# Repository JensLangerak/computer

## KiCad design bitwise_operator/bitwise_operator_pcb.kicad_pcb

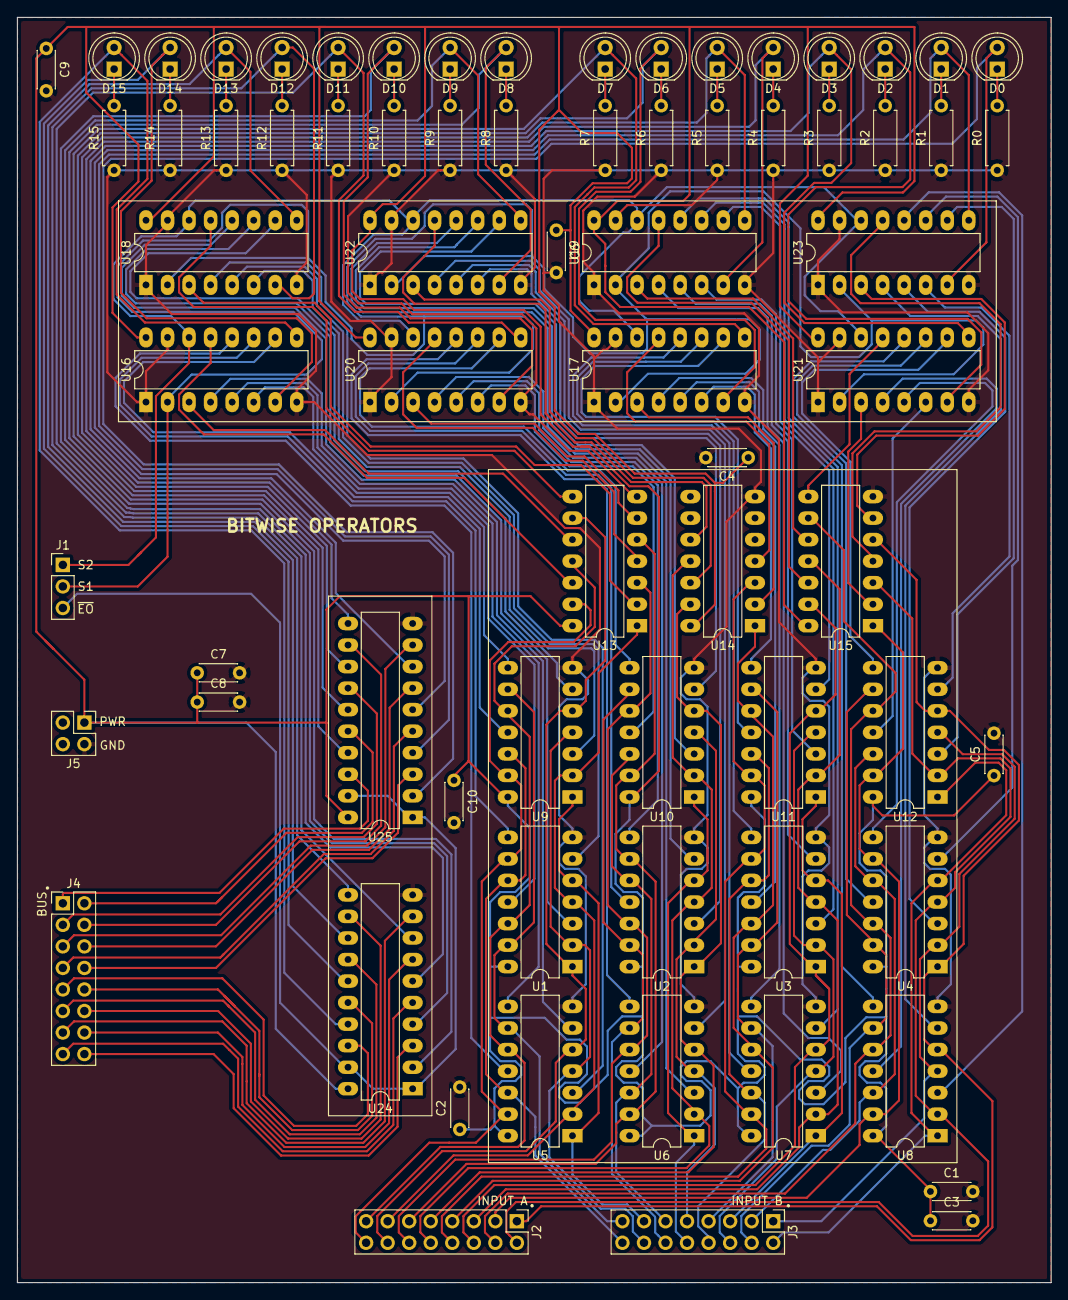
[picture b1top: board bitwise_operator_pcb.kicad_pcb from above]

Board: 2 copper layers, 121.9 x 149.2 mm, 72 parts (0 on the bottom side), 149 nets.

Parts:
C1, C2, C3, C4, C5, C6, C7, C8, C9, C10: 0.1µF; C_Disc_D4.3mm_W1.9mm_P5.00mm
D0, D1, D2, D3, D4, D5, D6, D7, D8, D9, D10, D11, D12, D13, D14, D15: LED_ALT; LED_D5.0mm
J1: Conn_01x03; PinHeader_1x03_P2.54mm_Vertical
J2, J3, J4: Conn_02x08_Odd_Even; PinHeader_2x08_P2.54mm_Vertical
J5: Conn_02x02_Odd_Even; PinHeader_2x02_P2.54mm_Vertical
R0, R1, R2, R3, R4, R5, R6, R7, R8, R9, R10, R11, R12, R13, R14, R15: 5k; R_Axial_DIN0207_L6.3mm_D2.5mm_P7.62mm_Horizontal
U1, U2, U3, U4: 74LS08; DIP-14_W7.62mm_LongPads
U5, U6, U7, U8: 74LS32; DIP-14_W7.62mm_LongPads
U9, U10, U11, U12: 74LS86; DIP-14_W7.62mm_LongPads
U13, U14, U15: 74LS04; DIP-14_W7.62mm_LongPads
U16, U17, U18, U19, U20, U21, U22, U23: 74LS153; DIP-16_W7.62mm_LongPads
U24, U25: 74LS244; DIP-20_W7.62mm_LongPads

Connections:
/CONN BUS A/D0: J2.1, U4.1, U8.5, U12.5, U15.5
/CONN BUS A/D1: J2.2, U4.4, U8.2, U12.2, U15.3
/CONN BUS A/D2: J2.3, U4.9, U8.13, U12.13, U15.1
/CONN BUS A/D3: J2.4, U4.12, U8.10, U12.10, U15.9
/CONN BUS A/D4: J2.5, U3.4, U7.2, U11.2, U15.11
/CONN BUS A/D5: J2.6, U3.1, U7.5, U11.5, U15.13
/CONN BUS A/D6: J2.7, U3.12, U7.10, U11.10, U14.1
/CONN BUS A/D7: J2.8, U3.9, U7.13, U11.13, U14.3
/CONN BUS A/D8: J2.9, U2.1, U6.5, U10.5, U14.13
/CONN BUS A/D9: J2.10, U2.4, U6.2, U10.2, U14.11
/CONN BUS A/D10: J2.11, U2.9, U6.13, U10.13, U13.5
/CONN BUS A/D11: J2.12, U2.12, U6.10, U10.10, U13.3
/CONN BUS A/D12: J2.13, U1.4, U5.2, U9.2, U13.1
/CONN BUS A/D13: J2.14, U1.1, U5.5, U9.5, U13.9
/CONN BUS A/D14: J2.15, U1.12, U5.10, U9.10, U13.11
/CONN BUS A/D15: J2.16, U1.9, U5.13, U9.13, U13.13
/CONN BUS B/D0: J3.1, U4.2, U8.4, U12.4
/CONN BUS B/D1: J3.2, U4.5, U8.1, U12.1
/CONN BUS B/D2: J3.3, U4.10, U8.12, U12.12
/CONN BUS B/D3: J3.4, U4.13, U8.9, U12.9
/CONN BUS B/D4: J3.5, U3.5, U7.1, U11.1
/CONN BUS B/D5: J3.6, U3.2, U7.4, U11.4
/CONN BUS B/D6: J3.7, U3.13, U7.9, U11.9
/CONN BUS B/D7: J3.8, U3.10, U7.12, U11.12
/CONN BUS B/D8: J3.9, U2.2, U6.4, U10.4
/CONN BUS B/D9: J3.10, U2.5, U6.1, U10.1
/CONN BUS B/D10: J3.11, U2.10, U6.12, U10.12
/CONN BUS B/D11: J3.12, U2.13, U6.9, U10.9
/CONN BUS B/D12: J3.13, U1.5, U5.1, U9.1
/CONN BUS B/D13: J3.14, U1.2, U5.4, U9.4
/CONN BUS B/D14: J3.15, U1.13, U5.9, U9.9
/CONN BUS B/D15: J3.16, U1.10, U5.12, U9.12
/CONN BUS DATA/D0: J4.1, U25.18
/CONN BUS DATA/D1: J4.2, U25.16
/CONN BUS DATA/D2: J4.3, U25.14
/CONN BUS DATA/D3: J4.4, U25.12
/CONN BUS DATA/D4: J4.5, U25.9
/CONN BUS DATA/D5: J4.6, U25.7
/CONN BUS DATA/D6: J4.7, U25.5
/CONN BUS DATA/D7: J4.8, U25.3
/CONN BUS DATA/D8: J4.9, U24.18
/CONN BUS DATA/D9: J4.10, U24.16
/CONN BUS DATA/D10: J4.11, U24.14
/CONN BUS DATA/D11: J4.12, U24.12
/CONN BUS DATA/D12: J4.13, U24.9
/CONN BUS DATA/D13: J4.14, U24.7
/CONN BUS DATA/D14: J4.15, U24.5
/CONN BUS DATA/D15: J4.16, U24.3
/LOGIC UNIT/BUS MULTIPLEXER/D_A0: U12.6, U23.6
/LOGIC UNIT/BUS MULTIPLEXER/D_A1: U12.3, U23.10
/LOGIC UNIT/BUS MULTIPLEXER/D_A2: U12.11, U21.6
/LOGIC UNIT/BUS MULTIPLEXER/D_A3: U12.8, U21.10
/LOGIC UNIT/BUS MULTIPLEXER/D_A4: U11.3, U19.6
/LOGIC UNIT/BUS MULTIPLEXER/D_A5: U11.6, U19.10
/LOGIC UNIT/BUS MULTIPLEXER/D_A6: U11.8, U17.6
/LOGIC UNIT/BUS MULTIPLEXER/D_A7: U11.11, U17.10
/LOGIC UNIT/BUS MULTIPLEXER/D_A8: U10.6, U22.6
/LOGIC UNIT/BUS MULTIPLEXER/D_A9: U10.3, U22.10
/LOGIC UNIT/BUS MULTIPLEXER/D_A10: U10.11, U20.6
/LOGIC UNIT/BUS MULTIPLEXER/D_A11: U10.8, U20.10
/LOGIC UNIT/BUS MULTIPLEXER/D_A12: U9.3, U18.6
/LOGIC UNIT/BUS MULTIPLEXER/D_A13: U9.6, U18.10
/LOGIC UNIT/BUS MULTIPLEXER/D_A14: U9.8, U16.6
/LOGIC UNIT/BUS MULTIPLEXER/D_A15: U9.11, U16.10
/LOGIC UNIT/BUS MULTIPLEXER/D_B0: U4.3, U23.5
/LOGIC UNIT/BUS MULTIPLEXER/D_B1: U4.6, U23.11
/LOGIC UNIT/BUS MULTIPLEXER/D_B2: U4.8, U21.5
/LOGIC UNIT/BUS MULTIPLEXER/D_B3: U4.11, U21.11
/LOGIC UNIT/BUS MULTIPLEXER/D_B4: U3.6, U19.5
/LOGIC UNIT/BUS MULTIPLEXER/D_B5: U3.3, U19.11
/LOGIC UNIT/BUS MULTIPLEXER/D_B6: U3.11, U17.5
/LOGIC UNIT/BUS MULTIPLEXER/D_B7: U3.8, U17.11
/LOGIC UNIT/BUS MULTIPLEXER/D_B8: U2.3, U22.5
/LOGIC UNIT/BUS MULTIPLEXER/D_B9: U2.6, U22.11
/LOGIC UNIT/BUS MULTIPLEXER/D_B10: U2.8, U20.5
/LOGIC UNIT/BUS MULTIPLEXER/D_B11: U2.11, U20.11
/LOGIC UNIT/BUS MULTIPLEXER/D_B12: U1.6, U18.5
/LOGIC UNIT/BUS MULTIPLEXER/D_B13: U1.3, U18.11
/LOGIC UNIT/BUS MULTIPLEXER/D_B14: U1.11, U16.5
/LOGIC UNIT/BUS MULTIPLEXER/D_B15: U1.8, U16.11
/LOGIC UNIT/BUS MULTIPLEXER/D_C0: U8.6, U23.4
/LOGIC UNIT/BUS MULTIPLEXER/D_C1: U8.3, U23.12
/LOGIC UNIT/BUS MULTIPLEXER/D_C2: U8.11, U21.4
/LOGIC UNIT/BUS MULTIPLEXER/D_C3: U8.8, U21.12
/LOGIC UNIT/BUS MULTIPLEXER/D_C4: U7.3, U19.4
/LOGIC UNIT/BUS MULTIPLEXER/D_C5: U7.6, U19.12
/LOGIC UNIT/BUS MULTIPLEXER/D_C6: U7.8, U17.4
/LOGIC UNIT/BUS MULTIPLEXER/D_C7: U7.11, U17.12
/LOGIC UNIT/BUS MULTIPLEXER/D_C8: U6.6, U22.4
/LOGIC UNIT/BUS MULTIPLEXER/D_C9: U6.3, U22.12
/LOGIC UNIT/BUS MULTIPLEXER/D_C10: U6.11, U20.4
/LOGIC UNIT/BUS MULTIPLEXER/D_C11: U6.8, U20.12
/LOGIC UNIT/BUS MULTIPLEXER/D_C12: U5.3, U18.4
/LOGIC UNIT/BUS MULTIPLEXER/D_C13: U5.6, U18.12
/LOGIC UNIT/BUS MULTIPLEXER/D_C14: U5.8, U16.4
/LOGIC UNIT/BUS MULTIPLEXER/D_C15: U5.11, U16.12
/LOGIC UNIT/BUS MULTIPLEXER/D_D0: U15.6, U23.3
/LOGIC UNIT/BUS MULTIPLEXER/D_D1: U15.4, U23.13
/LOGIC UNIT/BUS MULTIPLEXER/D_D2: U15.2, U21.3
/LOGIC UNIT/BUS MULTIPLEXER/D_D3: U15.8, U21.13
/LOGIC UNIT/BUS MULTIPLEXER/D_D4: U15.10, U19.3
/LOGIC UNIT/BUS MULTIPLEXER/D_D5: U15.12, U19.13
/LOGIC UNIT/BUS MULTIPLEXER/D_D6: U14.2, U17.3
/LOGIC UNIT/BUS MULTIPLEXER/D_D7: U14.4, U17.13
/LOGIC UNIT/BUS MULTIPLEXER/D_D8: U14.12, U22.3
/LOGIC UNIT/BUS MULTIPLEXER/D_D9: U14.10, U22.13
/LOGIC UNIT/BUS MULTIPLEXER/D_D10: U13.6, U20.3
/LOGIC UNIT/BUS MULTIPLEXER/D_D11: U13.4, U20.13
/LOGIC UNIT/BUS MULTIPLEXER/D_D12: U13.2, U18.3
/LOGIC UNIT/BUS MULTIPLEXER/D_D13: U13.8, U18.13
/LOGIC UNIT/BUS MULTIPLEXER/D_D14: U13.10, U16.3
/LOGIC UNIT/BUS MULTIPLEXER/D_D15: U13.12, U16.13
/LOGIC UNIT/LEDS/D0: D0.2, U23.7, U25.2
/LOGIC UNIT/LEDS/D1: D1.2, U23.9, U25.4
/LOGIC UNIT/LEDS/D2: D2.2, U21.7, U25.6
/LOGIC UNIT/LEDS/D3: D3.2, U21.9, U25.8
/LOGIC UNIT/LEDS/D4: D4.2, U19.7, U25.11
/LOGIC UNIT/LEDS/D5: D5.2, U19.9, U25.13
/LOGIC UNIT/LEDS/D6: D6.2, U17.7, U25.15
/LOGIC UNIT/LEDS/D7: D7.2, U17.9, U25.17
/LOGIC UNIT/LEDS/D8: D8.2, U22.7, U24.2
/LOGIC UNIT/LEDS/D9: D9.2, U22.9, U24.4
/LOGIC UNIT/LEDS/D10: D10.2, U20.7, U24.6
/LOGIC UNIT/LEDS/D11: D11.2, U20.9, U24.8
/LOGIC UNIT/LEDS/D12: D12.2, U18.7, U24.11
/LOGIC UNIT/LEDS/D13: D13.2, U18.9, U24.13
/LOGIC UNIT/LEDS/D14: D14.2, U16.7, U24.15
/LOGIC UNIT/LEDS/D15: D15.2, U16.9, U24.17
/LOGIC UNIT/S0: J1.1, U16.14, U17.14, U18.14, U19.14, U20.14, U21.14, U22.14, U23.14
/LOGIC UNIT/S1: J1.2, U16.2, U17.2, U18.2, U19.2, U20.2, U21.2, U22.2, U23.2
/LOGIC UNIT/~EO~: J1.3, U24.1, U24.19, U25.1, U25.19
GND: C1.2, C2.2, C3.2, C4.2, C5.2, C6.2, C7.2, C8.2, C9.2, C10.2, J5.2, R0.1, R1.1, R2.1, R3.1, R4.1, R5.1, R6.1, R7.1, R8.1, R9.1, R10.1, R11.1, R12.1, R13.1, R14.1, R15.1, U1.7, U2.7, U3.7, U4.7, U5.7, U6.7, U7.7, U8.7, U9.7, U10.7, U11.7, U12.7, U13.7, U14.7, U15.7, U16.1, U16.8, U16.15, U17.1, U17.8, U17.15, U18.1, U18.8, U18.15, U19.1, U19.8, U19.15, U20.1, U20.8, U20.15, U21.1, U21.8, U21.15, U22.1, U22.8, U22.15, U23.1, U23.8, U23.15, U24.10, U25.10
unnamed: D0.1, R0.2
unnamed: D1.1, R1.2
unnamed: D2.1, R2.2
unnamed: D3.1, R3.2
unnamed: D4.1, R4.2
unnamed: D5.1, R5.2
unnamed: D6.1, R6.2
unnamed: D7.1, R7.2
unnamed: D8.1, R8.2
unnamed: D9.1, R9.2
unnamed: D10.1, R10.2
unnamed: D11.1, R11.2
unnamed: D12.1, R12.2
unnamed: D13.1, R13.2
unnamed: D14.1, R14.2
unnamed: D15.1, R15.2
VCC: C1.1, C2.1, C3.1, C4.1, C5.1, C6.1, C7.1, C8.1, C9.1, C10.1, J5.1, U1.14, U2.14, U3.14, U4.14, U5.14, U6.14, U7.14, U8.14, U9.14, U10.14, U11.14, U12.14, U13.14, U14.14, U15.14, U16.16, U17.16, U18.16, U19.16, U20.16, U21.16, U22.16, U23.16, U24.20, U25.20

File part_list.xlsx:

| 4x | register | dus voor 2 onderdelen
 |  |  |  |  |  |  |  |  |  | Reg extra: | 1 |  |  |  |  |  |  | LS |  |  |  |  |  | HCT
 | ALU | Bit shifter | Bitwise Operator | Buttons | CU | Display | Memory | Mem programmer | Program counter | Register | Register Extra |  |  |  |  | TOT= | Shop unit cost | reichelt | mouser | conrad | kiwi |  |  | reichelt | mouser | conrad
Capacitor 0.1uF | 4 | 3 | 10 | 2 | 5 | 2 | 2 | 4 | 3 | 2 | 2 |  |  |  |  | 39
RED LED | 16 | 16 | 16 | 5 | 60 |  | 16 | 2 | 16 | 16 | 16 |  |  |  |  | 179 |  | 9.0999999999999998E-2
PIN HEADER | 42 | 24 | 23 | 22 | 107 | 26 | 38 |  | 24 | 22 | 22 |  |  |  |  | 350 |  | 0,03 (per 8)
Resitor 5K | 16 | 16 | 16 | 10 | 83 |  | 16 |  | 16 | 16 | 16 |  |  |  |  | 205
SW_PUSH |  |  |  | 5 | 1 |  |  |  |  |  | 0 |  |  |  |  | 6
Capacitor 1uF MKP4-250 ? of mks probeer allebij |  |  |  |  |  | 9 |  |  |  |  | 0 |  |  |  |  | 9
Resitor 220 |  |  |  |  |  |  |  | 2 |  |  | 0 |  |  |  |  | 2
Long pinheader arduino Stapel Header, normale pin headers |  |  |  |  |  |  |  | 34 |  |  | 0 |  |  |  |  | 34 |  |  |  |  | 2.5
Resistor 50K |  |  |  |  |  |  |  |  | 1 |  | 0 |  |  |  |  | 1
 |  |  |  |  |  |  |  |  |  |  | 0 |  |  |  |  | 0
74LS00 | 1 |  |  |  |  |  |  |  |  |  | 0 |  |  |  |  | 1 |  | 1.01 | 0.54 |  |  |  |  | 0.34 | 0.40699999999999997
74LS02 | 2 |  |  |  |  |  |  |  |  |  | 0 |  |  |  |  | 2 |  | 0.62 | 0.55100000000000005 |  |  |  |  | 0.3 | 0.40699999999999997
74LS04 |  |  | 3 | 1 | 1 |  | 1 |  |  |  | 0 |  |  |  |  | 6 |  | 0.68 | 0.61799999999999999 |  |  |  |  | 0.24 | 0.40699999999999997
74LS08 | 2 |  | 4 |  | 1 |  |  |  |  |  | 0 |  |  |  |  | 7 |  | 0.7 | 0.55900000000000005 |  |  |  |  | 0.22 | 0.40699999999999997
74LS139 |  |  |  |  |  |  |  | 1 |  |  | 0 |  |  |  |  | 1 |  | 0.82 | 0.71099999999999997 |  |  |  |  | 0.53 | 0.38100000000000001
74LS153 |  |  | 8 |  |  |  |  |  |  |  | 0 |  |  |  |  | 8 |  | 0.26 | 0.76200000000000001 |  |  |  |  | 0.23 | 0.55900000000000005
74LS163 |  |  |  |  | 1 |  |  |  | 4 |  | 0 |  |  |  |  | 5 |  | 0.44 | 0.66900000000000004 |  |  |  |  | 0.28000000000000003 | 0.5
74LS194 |  | 4 |  |  |  |  |  |  |  |  | 0 |  |  |  |  | 4 |  | 0.8 | 1.32 |  |  |  |  |  | 0.70299999999999996
74LS244 | 2 | 2 | 2 | 2 | 2 | 2 |  |  | 2 | 2 | 2 |  |  |  |  | 18 |  | 0.79 | 0.76200000000000001 |  |  |  |  | 0.37 | 0.49099999999999999
74LS245 |  |  |  |  |  |  | 2 | 1 |  |  | 0 |  |  |  |  | 3 |  | 0.82 |  |  |  |  |  | 0.45
74LS283 | 4 |  |  |  |  |  |  |  |  |  | 0 |  |  |  |  | 4 |  |  |  |  |  |  |  |  |  | 0.76
74LS32 |  |  | 4 |  |  |  |  |  |  |  | 0 |  |  |  |  | 4 |  | 0.57999999999999996 | 0.51700000000000002 |  |  |  |  | 0.55000000000000004 | 0.40699999999999997
74LS375 |  |  |  | 2 |  |  |  |  |  |  | 0 |  |  |  |  | 2 |  | 0.32 | 0.97399999999999998
74LS377 |  |  |  |  |  |  |  | 3 |  | 2 | 2 |  |  |  |  | 7 |  |  | 0.76200000000000001 |  |  |  |  | 0.39 | 0.55900000000000005
74LS386 MOET waarschijnlijk 136 zijn, prijzen daarvoor, denk eigenlijk 86, dus 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 | 4 |  |  |  |  |  |  |  |  |  | 0 |  |  |  |  | 4 |  |  | 0.72799999999999998 |  |  |  |  |  | 0.65200000000000002
74LS86 |  |  | 4 |  |  |  |  |  |  |  | 0 |  |  |  |  | 4 |  | 0.7 | 0.51700000000000002 |  |  |  |  |  | 0.58399999999999996
 |  |  |  |  |  |  |  |  |  |  | 0 |  |  |  |  | 0
 |  |  |  |  |  |  |  |  |  |  | 0 |  |  |  |  | 0
 |  |  |  |  |  |  |  |  |  |  | 0 |  |  |  |  | 0
Header jumpers |  |  |  |  | 8 |  |  |  |  |  | 0 |  |  |  |  | 8 |  | 0.02
SST39SF010A-70-4C-PHE |  |  |  |  | 6 |  |  |  |  |  | 0 |  |  |  |  | 6 |  | 1.68 | 1.05 | 1.94
SOCKET SST39SF010A-70-4C-PHE pin 32: w: 15:24 |  |  |  |  | 6 |  |  | 1 |  |  | 0 |  |  |  |  | 7 |  | 0.54 | 1.3 |  |  |  |  | https://www.reichelt.nl/ic-socket-32-polig-super-plat-gedraa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
NHD-C12864LZ-FSW-FBW-3V3 |  |  |  |  |  | 1 |  |  |  |  | 0 |  |  |  |  | 1 |  |  | 13.91
CD40109BE |  |  |  |  |  | 4 |  |  |  |  | 0 |  |  |  |  | 4 |  |  | 0.747
LP2950-3.0_TO92 of MCP1702-3002E/TO TODO nog beslitssen |  |  |  |  |  | 1 |  |  |  |  | 0 |  |  |  |  | 1
AT28C256-15PU |  |  |  |  |  |  | 2 |  |  |  | 0 |  |  |  |  | 2 |  | 10.69 | 7.52
SOCKETS AT28C256-15PU |  |  |  |  |  |  | 2 | 1 |  |  | 0 |  |  |  |  | 3 |  | 0.47 | 0.39
Control LEDS (BLUE) |  |  |  |  | 48 |  |  |  |  |  |  |  |  |  |  | 48 |  | 0.28000000000000003
CLK LED (GREEN) |  |  |  |  | 1 |  |  |  |  |  |  |  |  |  |  | 1 |  | 0.17299999999999999
COUNTER LED (BLUE) |  |  |  |  | 4 |  |  |  |  |  |  |  |  |  |  | 4 |  | 0.28000000000000003
FLAG LEDS (ORANGE) |  |  |  |  | 4 |  |  |  |  |  |  |  |  |  |  | 4
YELLOW LED |  |  |  |  |  |  |  |  |  |  |  |  |  |  |  |  |  | 0.14199999999999999
white |  |  |  |  |  |  |  |  |  |  |  |  |  |  |  |  |  | 0.24

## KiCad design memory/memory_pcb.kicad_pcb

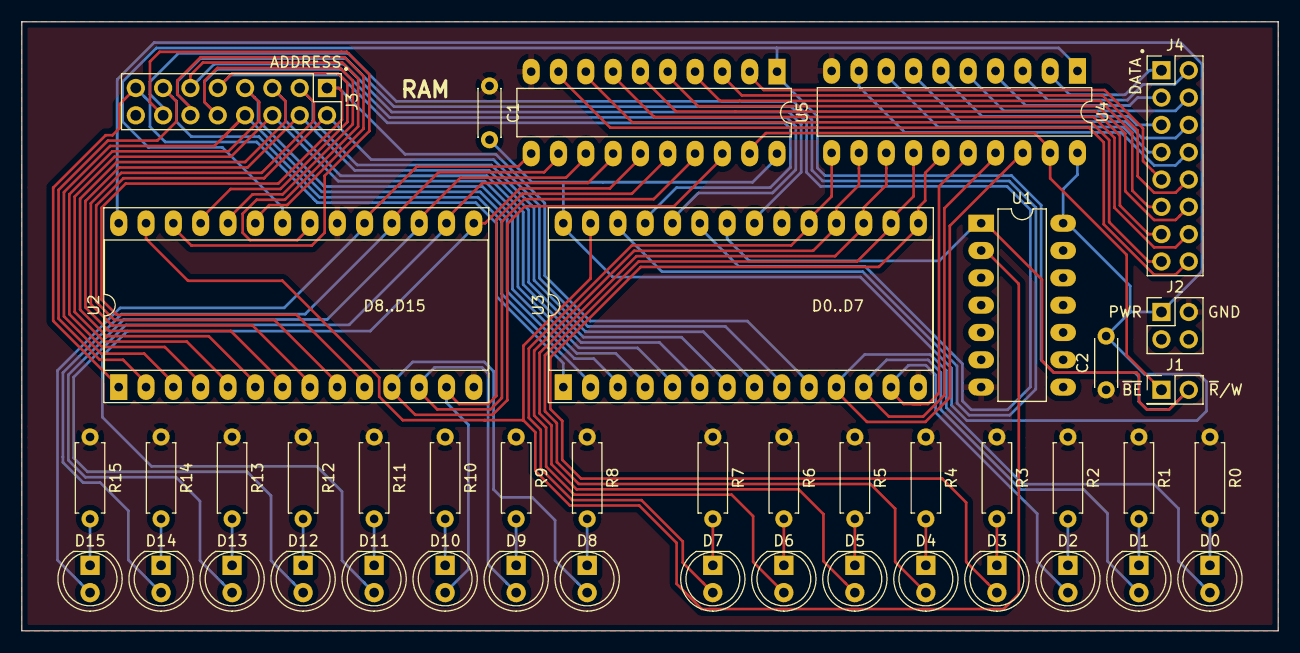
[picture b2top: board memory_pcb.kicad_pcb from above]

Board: 2 copper layers, 116.8 x 56.6 mm, 43 parts (0 on the bottom side), 68 nets.

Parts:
C1, C2: 0.1µF; C_Disc_D4.3mm_W1.9mm_P5.00mm
D0, D1, D2, D3, D4, D5, D6, D7, D8, D9, D10, D11, D12, D13, D14, D15: LED_ALT; LED_D5.0mm
J1: Conn_02x01; PinHeader_2x01_P2.54mm_Vertical
J2: Conn_02x02_Odd_Even; PinHeader_2x02_P2.54mm_Vertical
J3, J4: Conn_02x08_Odd_Even; PinHeader_2x08_P2.54mm_Vertical
R0, R1, R2, R3, R4, R5, R6, R7, R8, R9, R10, R11, R12, R13, R14, R15: 5k; R_Axial_DIN0207_L6.3mm_D2.5mm_P7.62mm_Horizontal
U1: 74LS04; DIP-14_W7.62mm_LongPads
U2, U3: AT28C256-15PU; DIP-28_W15.24mm_Socket_LongPads
U4, U5: 74LS245; DIP-20_W7.62mm_LongPads

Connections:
/CON BUS DATA/D0: J4.1, U4.2
/CON BUS DATA/D1: J4.2, U4.3
/CON BUS DATA/D2: J4.3, U4.4
/CON BUS DATA/D3: J4.4, U4.5
/CON BUS DATA/D4: J4.5, U4.6
/CON BUS DATA/D5: J4.6, U4.7
/CON BUS DATA/D6: J4.7, U4.8
/CON BUS DATA/D7: J4.8, U4.9
/CON BUS DATA/D8: J4.9, U5.2
/CON BUS DATA/D9: J4.10, U5.3
/CON BUS DATA/D10: J4.11, U5.4
/CON BUS DATA/D11: J4.12, U5.5
/CON BUS DATA/D12: J4.13, U5.6
/CON BUS DATA/D13: J4.14, U5.7
/CON BUS DATA/D14: J4.15, U5.8
/CON BUS DATA/D15: J4.16, U5.9
/memory/A0: J3.1, U2.10, U3.10
/memory/A1: J3.2, U2.9, U3.9
/memory/A2: J3.3, U2.8, U3.8
/memory/A3: J3.4, U2.7, U3.7
/memory/A4: J3.5, U2.6, U3.6
/memory/A5: J3.6, U2.5, U3.5
/memory/A6: J3.7, U2.4, U3.4
/memory/A7: J3.8, U2.3, U3.3
/memory/A8: J3.9, U2.25, U3.25
/memory/A9: J3.10, U2.24, U3.24
/memory/A10: J3.11, U2.21, U3.21
/memory/A11: J3.12, U2.23, U3.23
/memory/A12: J3.13, U2.2, U3.2
/memory/A13: J3.14, U2.26, U3.26
/memory/A14: J3.15, U2.1, U3.1
/memory/D0: D0.2, U3.11, U4.18
/memory/D1: D1.2, U3.12, U4.17
/memory/D2: D2.2, U3.13, U4.16
/memory/D3: D3.2, U3.15, U4.15
/memory/D4: D4.2, U3.16, U4.14
/memory/D5: D5.2, U3.17, U4.13
/memory/D6: D6.2, U3.18, U4.12
/memory/D7: D7.2, U3.19, U4.11
/memory/D8: D8.2, U2.11, U5.18
/memory/D9: D9.2, U2.12, U5.17
/memory/D10: D10.2, U2.13, U5.16
/memory/D11: D11.2, U2.15, U5.15
/memory/D12: D12.2, U2.16, U5.14
/memory/D13: D13.2, U2.17, U5.13
/memory/D14: D14.2, U2.18, U5.12
/memory/D15: D15.2, U2.19, U5.11
/memory/~WE~: U1.2, U2.27, U3.27
/~BE~: J1.1, U4.19, U5.19
/~R~-W: J1.2, U1.1, U2.22, U3.22, U4.1, U5.1
GND: C1.1, C2.1, J2.2, R0.1, R1.1, R2.1, R3.1, R4.1, R5.1, R6.1, R7.1, R8.1, R9.1, R10.1, R11.1, R12.1, R13.1, R14.1, R15.1, U1.7, U2.14, U2.20, U3.14, U3.20, U4.10, U5.10
unnamed: D0.1, R0.2
unnamed: D1.1, R1.2
unnamed: D2.1, R2.2
unnamed: D3.1, R3.2
unnamed: D4.1, R4.2
unnamed: D5.1, R5.2
unnamed: D6.1, R6.2
unnamed: D7.1, R7.2
unnamed: D8.1, R8.2
unnamed: D9.1, R9.2
unnamed: D10.1, R10.2
unnamed: D11.1, R11.2
unnamed: D12.1, R12.2
unnamed: D13.1, R13.2
unnamed: D14.1, R14.2
unnamed: D15.1, R15.2
VCC: C1.2, C2.2, J2.1, U1.14, U2.28, U3.28, U4.20, U5.20

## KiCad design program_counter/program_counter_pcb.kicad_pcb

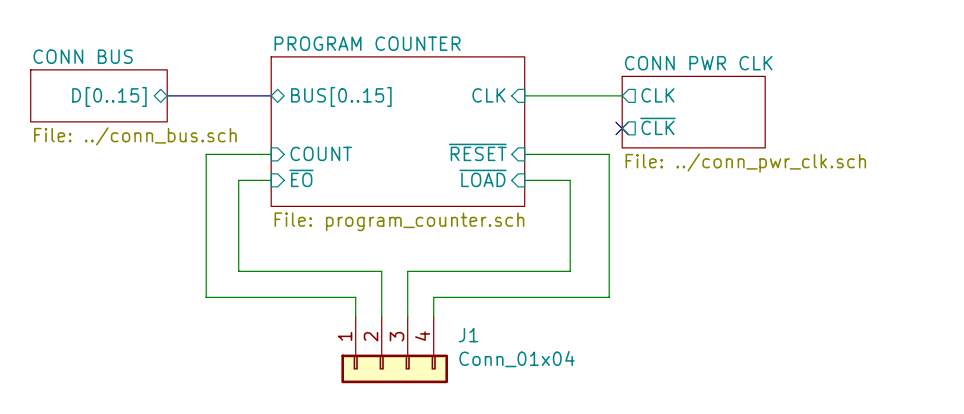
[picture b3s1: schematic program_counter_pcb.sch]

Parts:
J1: Conn_01x04; PinHeader_1x04_P2.54mm_Vertical

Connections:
/PROGRAM COUNTER/COUNT: J1.1; also elsewhere on the board
/PROGRAM COUNTER/~EO~: J1.2; also elsewhere on the board
/PROGRAM COUNTER/~LOAD~: J1.3; also elsewhere on the board
/PROGRAM COUNTER/~RESET~: J1.4; also elsewhere on the board

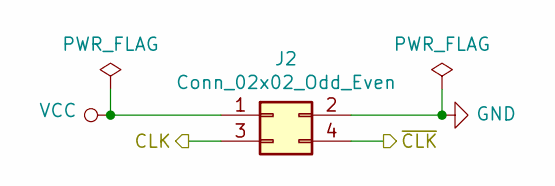
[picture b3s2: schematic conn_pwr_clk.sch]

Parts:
J2: Conn_02x02_Odd_Even; PinHeader_2x02_P2.54mm_Vertical

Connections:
/CONN PWR CLK/CLK: J2.3; also elsewhere on the board
/CONN PWR CLK/~CLK~: J2.4
GND: J2.2; also elsewhere on the board
VCC: J2.1; also elsewhere on the board

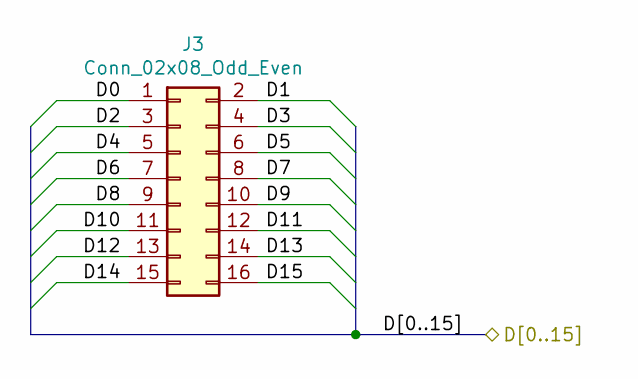
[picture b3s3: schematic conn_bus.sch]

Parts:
J3: Conn_02x08_Odd_Even; PinHeader_2x08_P2.54mm_Vertical

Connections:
/PROGRAM COUNTER/B0: J3.1; also elsewhere on the board
/PROGRAM COUNTER/B1: J3.2; also elsewhere on the board
/PROGRAM COUNTER/B2: J3.3; also elsewhere on the board
/PROGRAM COUNTER/B3: J3.4; also elsewhere on the board
/PROGRAM COUNTER/B4: J3.5; also elsewhere on the board
/PROGRAM COUNTER/B5: J3.6; also elsewhere on the board
/PROGRAM COUNTER/B6: J3.7; also elsewhere on the board
/PROGRAM COUNTER/B7: J3.8; also elsewhere on the board
/PROGRAM COUNTER/B8: J3.9; also elsewhere on the board
/PROGRAM COUNTER/B9: J3.10; also elsewhere on the board
/PROGRAM COUNTER/B10: J3.11; also elsewhere on the board
/PROGRAM COUNTER/B11: J3.12; also elsewhere on the board
/PROGRAM COUNTER/B12: J3.13; also elsewhere on the board
/PROGRAM COUNTER/B13: J3.14; also elsewhere on the board
/PROGRAM COUNTER/B14: J3.15; also elsewhere on the board
/PROGRAM COUNTER/B15: J3.16; also elsewhere on the board

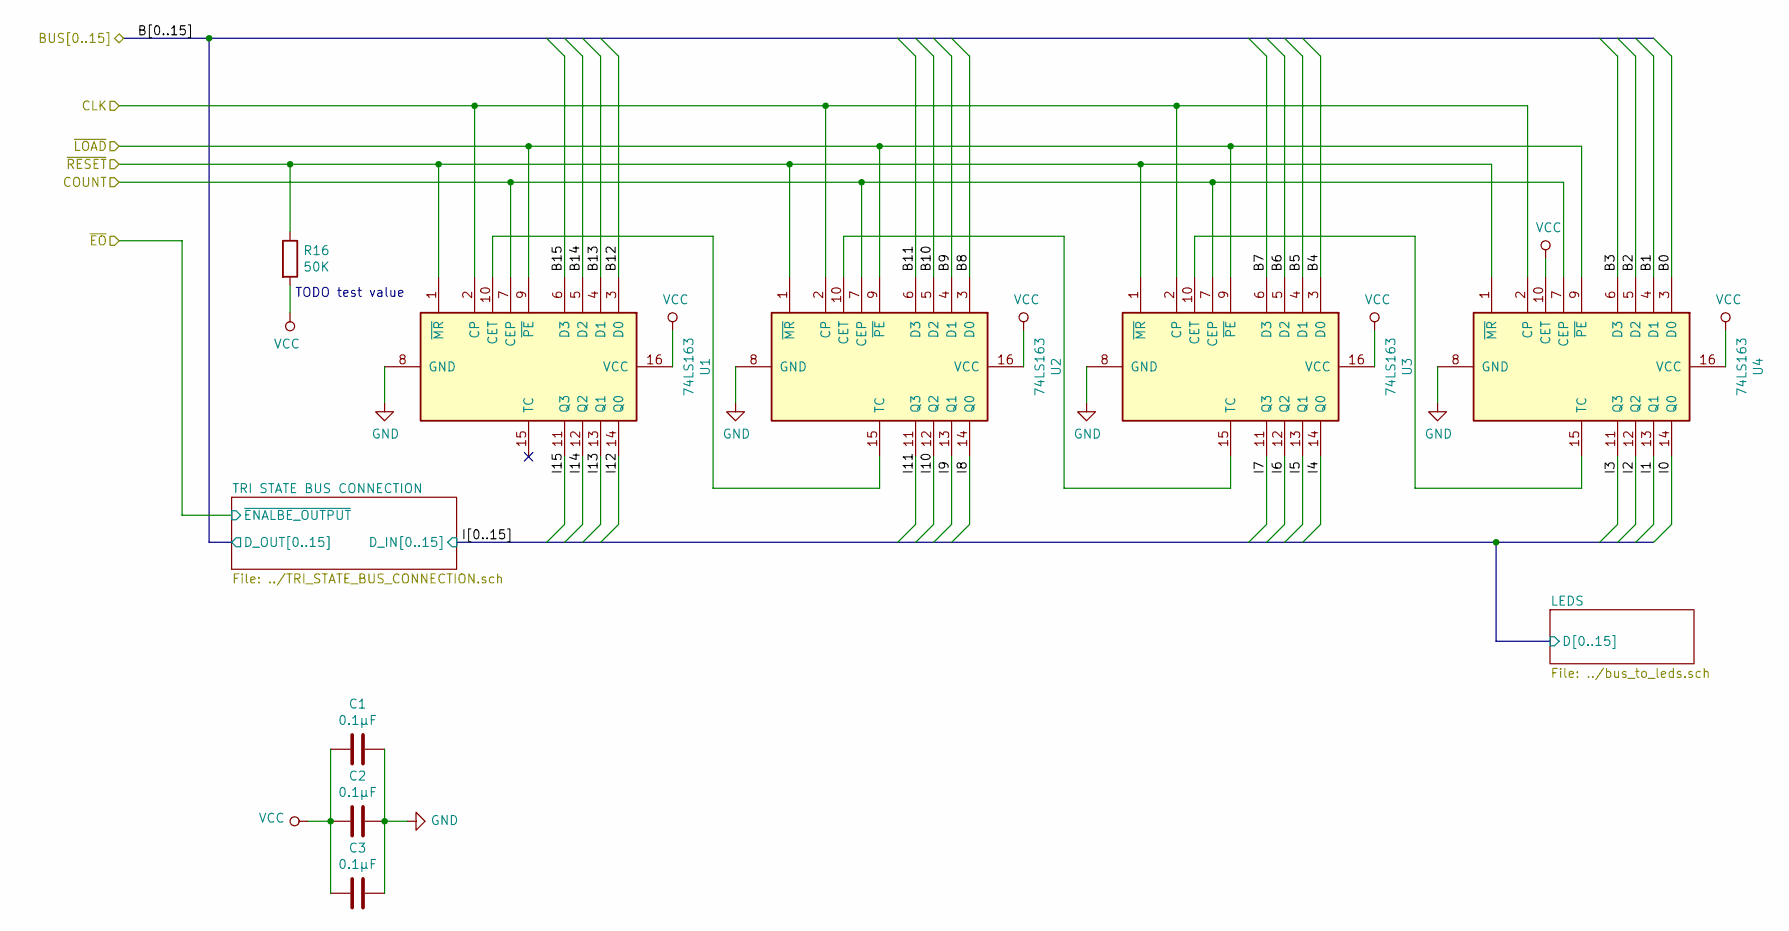
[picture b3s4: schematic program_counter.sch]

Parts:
C1, C2, C3: 0.1µF; C_Disc_D4.3mm_W1.9mm_P5.00mm
R16: 50K; R_Axial_DIN0207_L6.3mm_D2.5mm_P7.62mm_Horizontal
U1, U2, U3, U4: 74LS163; DIP-16_W7.62mm_LongPads

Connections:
/CONN PWR CLK/CLK: U1.2 (CP), U2.2 (CP), U3.2 (CP), U4.2 (CP); also elsewhere on the board
/PROGRAM COUNTER/B0: U4.3 (D0); also elsewhere on the board
/PROGRAM COUNTER/B1: U4.4 (D1); also elsewhere on the board
/PROGRAM COUNTER/B2: U4.5 (D2); also elsewhere on the board
/PROGRAM COUNTER/B3: U4.6 (D3); also elsewhere on the board
/PROGRAM COUNTER/B4: U3.3 (D0); also elsewhere on the board
/PROGRAM COUNTER/B5: U3.4 (D1); also elsewhere on the board
/PROGRAM COUNTER/B6: U3.5 (D2); also elsewhere on the board
/PROGRAM COUNTER/B7: U3.6 (D3); also elsewhere on the board
/PROGRAM COUNTER/B8: U2.3 (D0); also elsewhere on the board
/PROGRAM COUNTER/B9: U2.4 (D1); also elsewhere on the board
/PROGRAM COUNTER/B10: U2.5 (D2); also elsewhere on the board
/PROGRAM COUNTER/B11: U2.6 (D3); also elsewhere on the board
/PROGRAM COUNTER/B12: U1.3 (D0); also elsewhere on the board
/PROGRAM COUNTER/B13: U1.4 (D1); also elsewhere on the board
/PROGRAM COUNTER/B14: U1.5 (D2); also elsewhere on the board
/PROGRAM COUNTER/B15: U1.6 (D3); also elsewhere on the board
/PROGRAM COUNTER/COUNT: U1.7 (CEP), U2.7 (CEP), U3.7 (CEP), U4.7 (CEP); also elsewhere on the board
/PROGRAM COUNTER/I0: U4.14 (Q0); also elsewhere on the board
/PROGRAM COUNTER/I1: U4.13 (Q1); also elsewhere on the board
/PROGRAM COUNTER/I2: U4.12 (Q2); also elsewhere on the board
/PROGRAM COUNTER/I3: U4.11 (Q3); also elsewhere on the board
/PROGRAM COUNTER/I4: U3.14 (Q0); also elsewhere on the board
/PROGRAM COUNTER/I5: U3.13 (Q1); also elsewhere on the board
/PROGRAM COUNTER/I6: U3.12 (Q2); also elsewhere on the board
/PROGRAM COUNTER/I7: U3.11 (Q3); also elsewhere on the board
/PROGRAM COUNTER/I8: U2.14 (Q0); also elsewhere on the board
/PROGRAM COUNTER/I9: U2.13 (Q1); also elsewhere on the board
/PROGRAM COUNTER/I10: U2.12 (Q2); also elsewhere on the board
/PROGRAM COUNTER/I11: U2.11 (Q3); also elsewhere on the board
/PROGRAM COUNTER/I12: U1.14 (Q0); also elsewhere on the board
/PROGRAM COUNTER/I13: U1.13 (Q1); also elsewhere on the board
/PROGRAM COUNTER/I14: U1.12 (Q2); also elsewhere on the board
/PROGRAM COUNTER/I15: U1.11 (Q3); also elsewhere on the board
/PROGRAM COUNTER/~LOAD~: U1.9 (~PE), U2.9 (~PE), U3.9 (~PE), U4.9 (~PE); also elsewhere on the board
/PROGRAM COUNTER/~RESET~: R16.1, U1.1 (~MR), U2.1 (~MR), U3.1 (~MR), U4.1 (~MR); also elsewhere on the board
GND: C1.1, C2.1, C3.1, U1.8 (GND), U2.8 (GND), U3.8 (GND), U4.8 (GND); also elsewhere on the board
unnamed: U1.10 (CET), U2.15 (TC)
unnamed: U2.10 (CET), U3.15 (TC)
unnamed: U3.10 (CET), U4.15 (TC)
VCC: C1.2, C2.2, C3.2, R16.2, U1.16 (VCC), U2.16 (VCC), U3.16 (VCC), U4.10 (CET), U4.16 (VCC); also elsewhere on the board

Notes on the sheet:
TODO test value

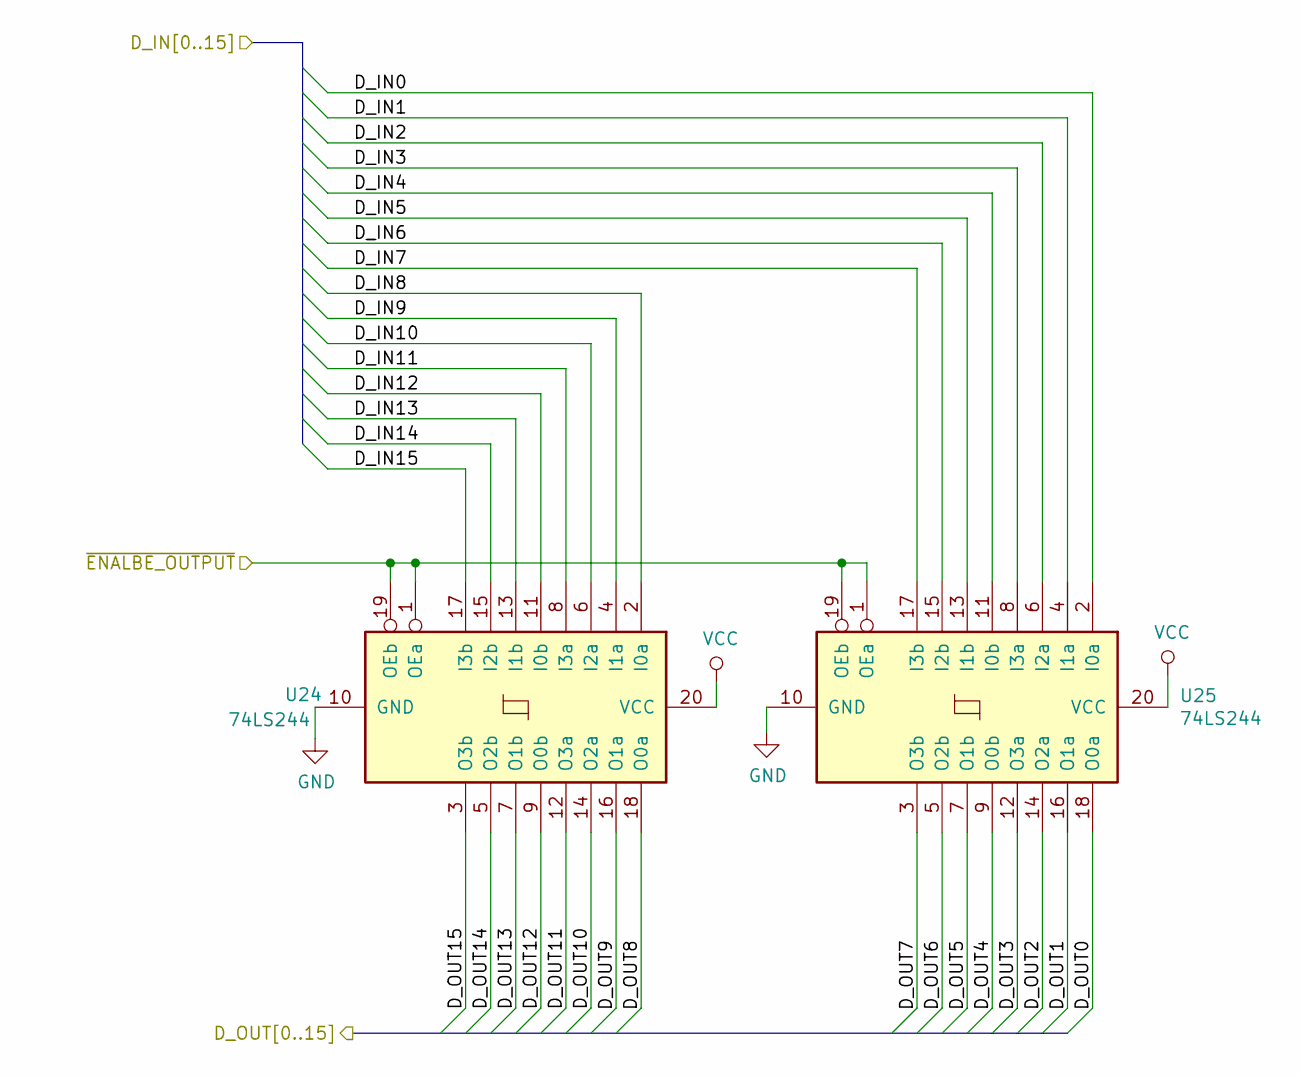
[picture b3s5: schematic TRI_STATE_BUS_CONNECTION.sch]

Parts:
U24, U25: 74LS244; DIP-20_W7.62mm_LongPads

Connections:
/PROGRAM COUNTER/B0: U25.18 (O0a); also elsewhere on the board
/PROGRAM COUNTER/B1: U25.16 (O1a); also elsewhere on the board
/PROGRAM COUNTER/B2: U25.14 (O2a); also elsewhere on the board
/PROGRAM COUNTER/B3: U25.12 (O3a); also elsewhere on the board
/PROGRAM COUNTER/B4: U25.9 (O0b); also elsewhere on the board
/PROGRAM COUNTER/B5: U25.7 (O1b); also elsewhere on the board
/PROGRAM COUNTER/B6: U25.5 (O2b); also elsewhere on the board
/PROGRAM COUNTER/B7: U25.3 (O3b); also elsewhere on the board
/PROGRAM COUNTER/B8: U24.18 (O0a); also elsewhere on the board
/PROGRAM COUNTER/B9: U24.16 (O1a); also elsewhere on the board
/PROGRAM COUNTER/B10: U24.14 (O2a); also elsewhere on the board
/PROGRAM COUNTER/B11: U24.12 (O3a); also elsewhere on the board
/PROGRAM COUNTER/B12: U24.9 (O0b); also elsewhere on the board
/PROGRAM COUNTER/B13: U24.7 (O1b); also elsewhere on the board
/PROGRAM COUNTER/B14: U24.5 (O2b); also elsewhere on the board
/PROGRAM COUNTER/B15: U24.3 (O3b); also elsewhere on the board
/PROGRAM COUNTER/I0: U25.2 (I0a); also elsewhere on the board
/PROGRAM COUNTER/I1: U25.4 (I1a); also elsewhere on the board
/PROGRAM COUNTER/I2: U25.6 (I2a); also elsewhere on the board
/PROGRAM COUNTER/I3: U25.8 (I3a); also elsewhere on the board
/PROGRAM COUNTER/I4: U25.11 (I0b); also elsewhere on the board
/PROGRAM COUNTER/I5: U25.13 (I1b); also elsewhere on the board
/PROGRAM COUNTER/I6: U25.15 (I2b); also elsewhere on the board
/PROGRAM COUNTER/I7: U25.17 (I3b); also elsewhere on the board
/PROGRAM COUNTER/I8: U24.2 (I0a); also elsewhere on the board
/PROGRAM COUNTER/I9: U24.4 (I1a); also elsewhere on the board
/PROGRAM COUNTER/I10: U24.6 (I2a); also elsewhere on the board
/PROGRAM COUNTER/I11: U24.8 (I3a); also elsewhere on the board
/PROGRAM COUNTER/I12: U24.11 (I0b); also elsewhere on the board
/PROGRAM COUNTER/I13: U24.13 (I1b); also elsewhere on the board
/PROGRAM COUNTER/I14: U24.15 (I2b); also elsewhere on the board
/PROGRAM COUNTER/I15: U24.17 (I3b); also elsewhere on the board
/PROGRAM COUNTER/~EO~: U24.1 (OEa), U24.19 (OEb), U25.1 (OEa), U25.19 (OEb); also elsewhere on the board
GND: U24.10 (GND), U25.10 (GND); also elsewhere on the board
VCC: U24.20 (VCC), U25.20 (VCC); also elsewhere on the board

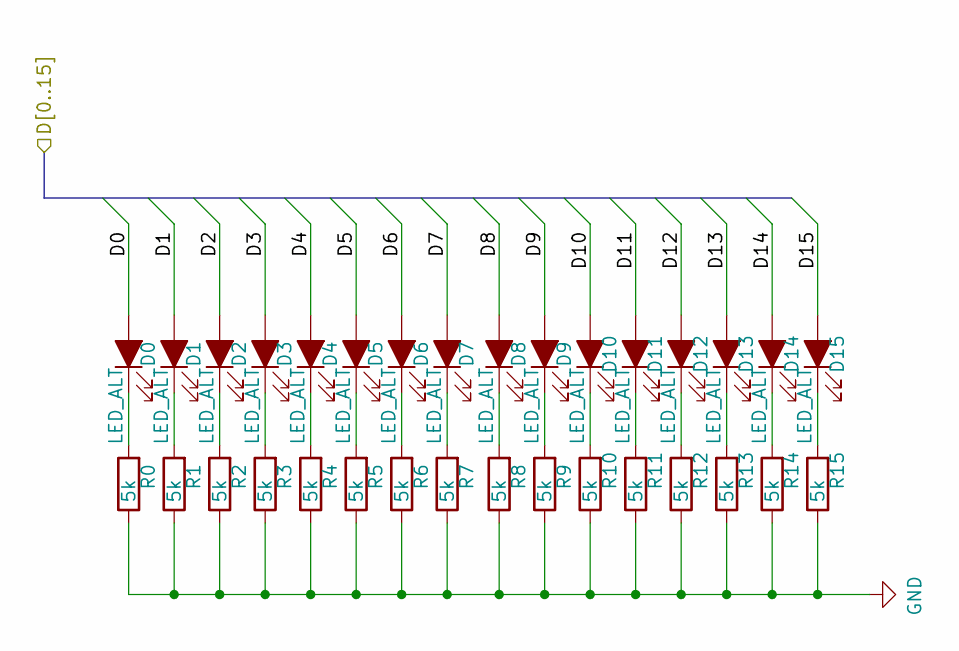
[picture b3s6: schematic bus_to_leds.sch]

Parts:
D0, D1, D2, D3, D4, D5, D6, D7, D8, D9, D10, D11, D12, D13, D14, D15: LED_ALT; LED_D5.0mm
R0, R1, R2, R3, R4, R5, R6, R7, R8, R9, R10, R11, R12, R13, R14, R15: 5k; R_Axial_DIN0207_L6.3mm_D2.5mm_P7.62mm_Horizontal

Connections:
/PROGRAM COUNTER/I0: D0.2 (A); also elsewhere on the board
/PROGRAM COUNTER/I1: D1.2 (A); also elsewhere on the board
/PROGRAM COUNTER/I2: D2.2 (A); also elsewhere on the board
/PROGRAM COUNTER/I3: D3.2 (A); also elsewhere on the board
/PROGRAM COUNTER/I4: D4.2 (A); also elsewhere on the board
/PROGRAM COUNTER/I5: D5.2 (A); also elsewhere on the board
/PROGRAM COUNTER/I6: D6.2 (A); also elsewhere on the board
/PROGRAM COUNTER/I7: D7.2 (A); also elsewhere on the board
/PROGRAM COUNTER/I8: D8.2 (A); also elsewhere on the board
/PROGRAM COUNTER/I9: D9.2 (A); also elsewhere on the board
/PROGRAM COUNTER/I10: D10.2 (A); also elsewhere on the board
/PROGRAM COUNTER/I11: D11.2 (A); also elsewhere on the board
/PROGRAM COUNTER/I12: D12.2 (A); also elsewhere on the board
/PROGRAM COUNTER/I13: D13.2 (A); also elsewhere on the board
/PROGRAM COUNTER/I14: D14.2 (A); also elsewhere on the board
/PROGRAM COUNTER/I15: D15.2 (A); also elsewhere on the board
GND: R0.1, R1.1, R2.1, R3.1, R4.1, R5.1, R6.1, R7.1, R8.1, R9.1, R10.1, R11.1, R12.1, R13.1, R14.1, R15.1; also elsewhere on the board
unnamed: D0.1 (K), R0.2
unnamed: D1.1 (K), R1.2
unnamed: D2.1 (K), R2.2
unnamed: D3.1 (K), R3.2
unnamed: D4.1 (K), R4.2
unnamed: D5.1 (K), R5.2
unnamed: D6.1 (K), R6.2
unnamed: D7.1 (K), R7.2
unnamed: D8.1 (K), R8.2
unnamed: D9.1 (K), R9.2
unnamed: D10.1 (K), R10.2
unnamed: D11.1 (K), R11.2
unnamed: D12.1 (K), R12.2
unnamed: D13.1 (K), R13.2
unnamed: D14.1 (K), R14.2
unnamed: D15.1 (K), R15.2

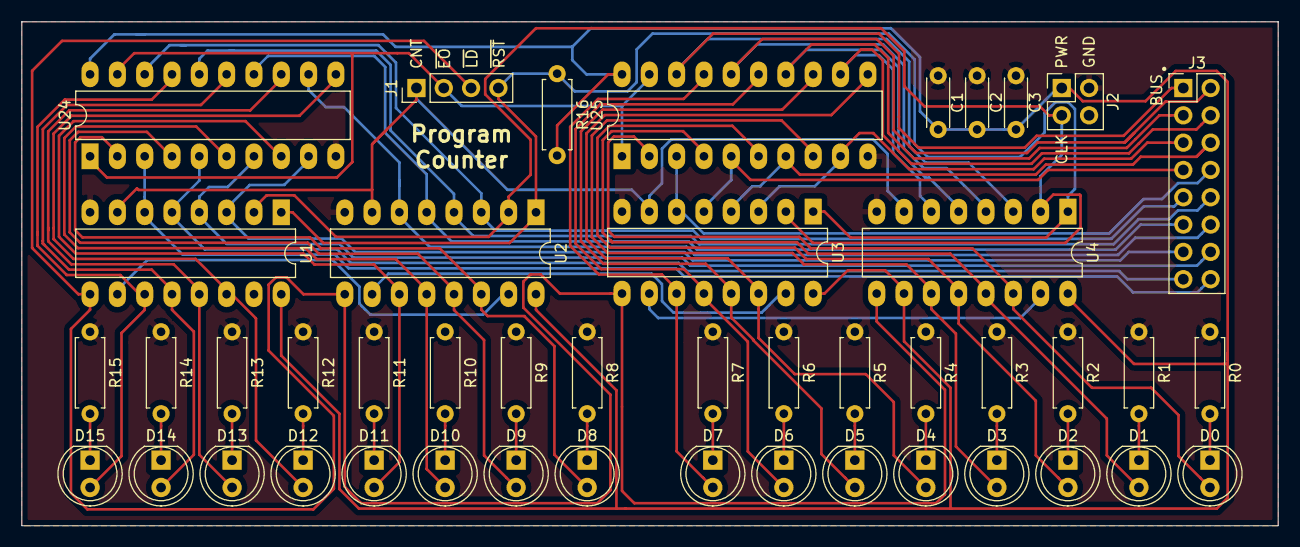
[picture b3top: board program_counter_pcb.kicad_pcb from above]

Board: 2 copper layers, 116.8 x 46.9 mm, 45 parts (0 on the bottom side), 58 nets.
